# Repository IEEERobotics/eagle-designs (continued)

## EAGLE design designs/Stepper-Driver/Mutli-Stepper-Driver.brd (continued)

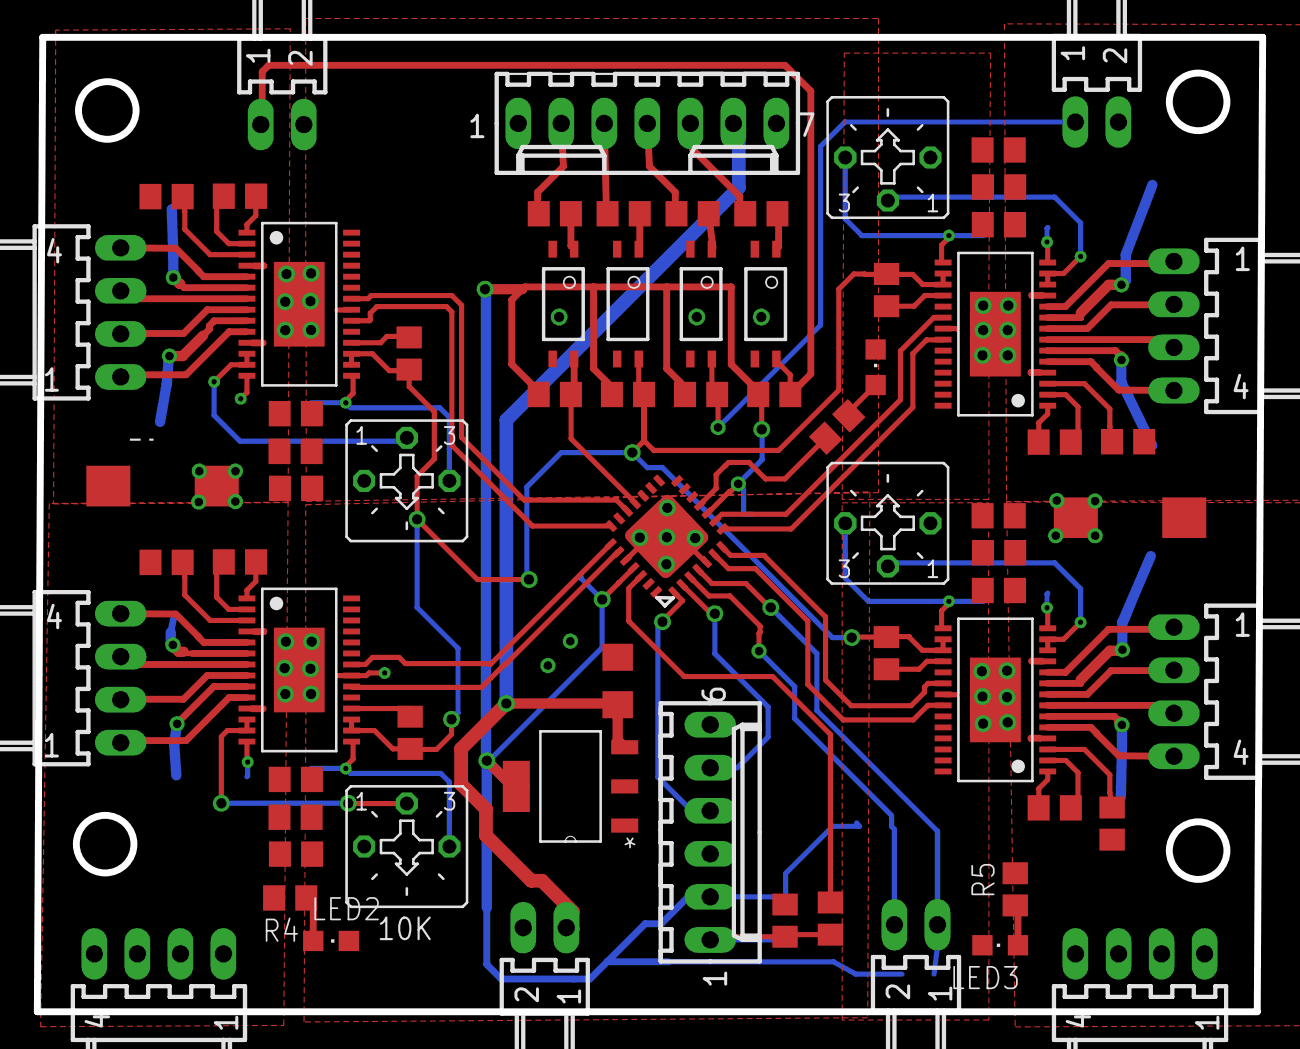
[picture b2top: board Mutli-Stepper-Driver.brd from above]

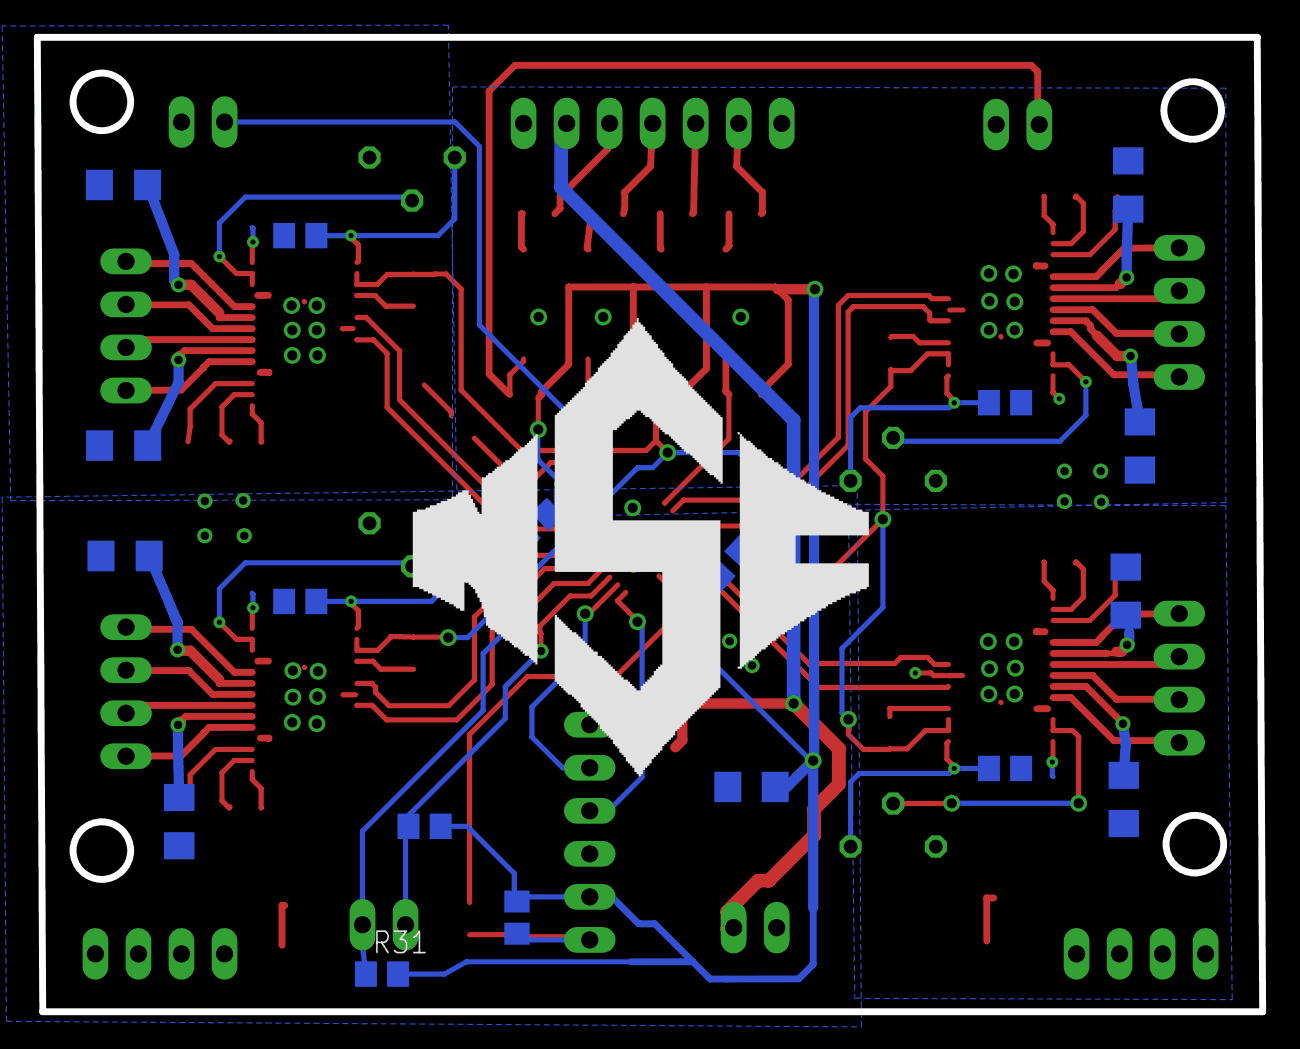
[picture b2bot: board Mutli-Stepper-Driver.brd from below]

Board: 2 copper layers, 72.3 x 57.5 mm, 87 parts (18 on the bottom side), 83 nets.

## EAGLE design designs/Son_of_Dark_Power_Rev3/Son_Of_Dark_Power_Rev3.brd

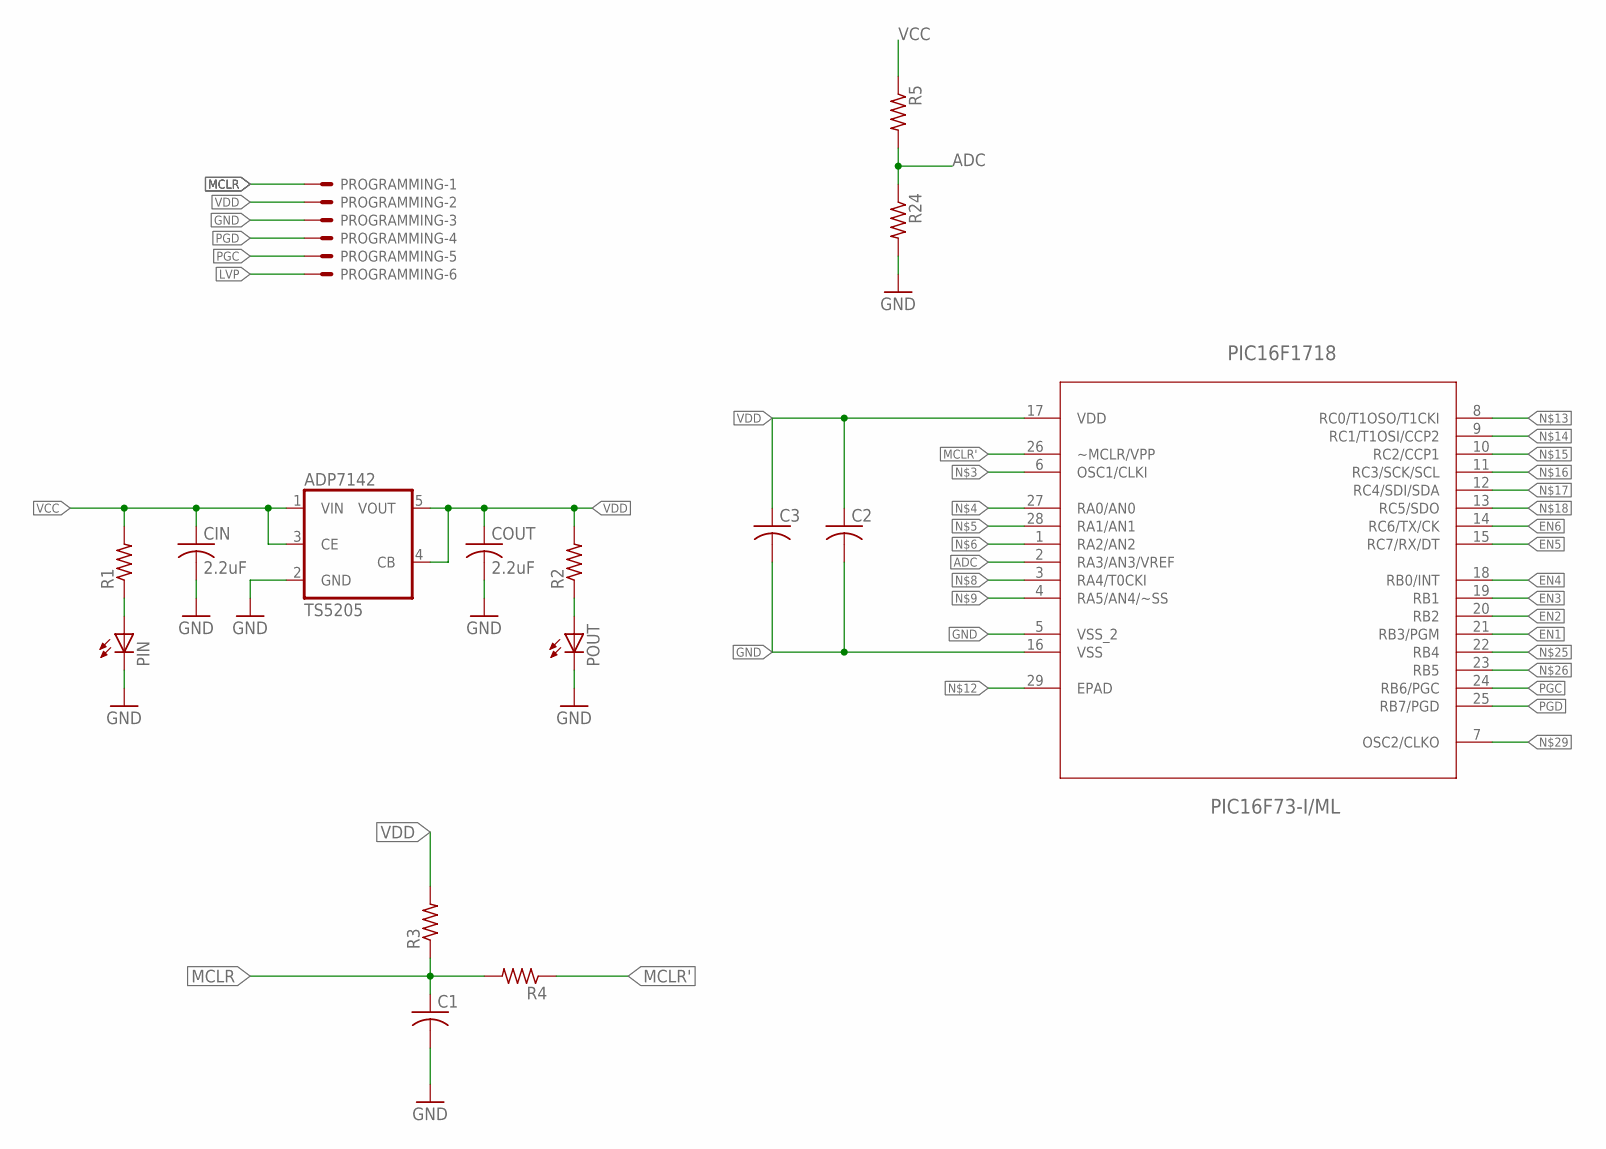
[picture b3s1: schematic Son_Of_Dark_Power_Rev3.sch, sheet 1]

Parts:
ADP7142: TS5205; SOT25
C1, C2, C3: C-USC0805; C0805
CIN: 2.2uF; C1206K
COUT: 2.2uF; C1206K
PIC16F1718: PIC16F73-I/ML; QFN65P600X600X100-28N
PIN: LEDCHIPLED_1206; CHIPLED_1206
POUT: LEDCHIPLED_1206; CHIPLED_1206
PROGRAMMING: 22-23-2061
R1, R2, R3, R4, R5, R24: R-US_R0805; R0805

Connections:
ADC: PIC16F1718.2 (RA3/AN3/VREF), R5.2, R24.1
EN1: PIC16F1718.21 (RB3/PGM); also elsewhere on the board
EN2: PIC16F1718.20 (RB2); also elsewhere on the board
EN3: PIC16F1718.19 (RB1); also elsewhere on the board
EN4: PIC16F1718.18 (RB0/INT); also elsewhere on the board
EN5: PIC16F1718.15 (RC7/RX/DT); also elsewhere on the board
EN6: PIC16F1718.14 (RC6/TX/CK); also elsewhere on the board
GND: ADP7142.2 (GND), C1.2, C2.2, C3.2, CIN.2, COUT.2, PIC16F1718.5 (VSS_2), PIC16F1718.16 (VSS), PIN.C, POUT.C, PROGRAMMING.3, R24.2; also elsewhere on the board
LVP: PROGRAMMING.6
MCLR: C1.1, PROGRAMMING.1, R3.1, R4.2
MCLR': PIC16F1718.26 (~MCLR/VPP), R4.1
unnamed: PIN.A, R1.1
unnamed: POUT.A, R2.1
PGC: PIC16F1718.24 (RB6/PGC), PROGRAMMING.5
PGD: PIC16F1718.25 (RB7/PGD), PROGRAMMING.4
VCC: ADP7142.1 (VIN), ADP7142.3 (CE), CIN.1, R1.2, R5.1; also elsewhere on the board
VDD: ADP7142.4 (CB), ADP7142.5 (VOUT), C2.1, C3.1, COUT.1, PIC16F1718.17 (VDD), PROGRAMMING.2, R2.2, R3.2

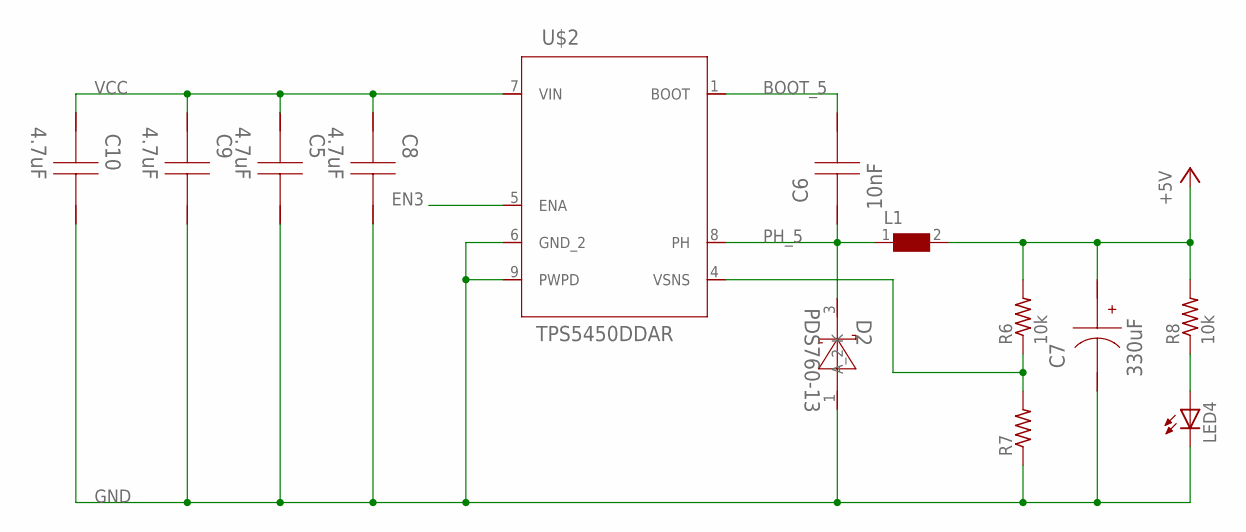
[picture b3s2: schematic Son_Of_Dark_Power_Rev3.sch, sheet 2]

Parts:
C5, C8, C9, C10: 4.7uF; 1206
C6: 10nF; 0805
C7: 330uF; SM_RADIAL_10AMM
D2: PDS760-13; POWERDI5
L1: WE-HCC-7443331000_1090; WE-HCC_1090
LED4: LEDSML1206; SML1206
R6: 10k; R1206
R7: R-US_R1206; R1206
R8: 10k; R0805
U$2: TPS5450DDAR; R-PDSO-G8

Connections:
BOOT_5: C6.1, U$2.1 (BOOT)
EN3: U$2.5 (ENA); also elsewhere on the board
GND: C5.1, C7.2 (-), C8.1, C9.1, C10.1, D2.1 (A_2), LED4.C, R7.1, U$2.6 (GND_2), U$2.9 (PWPD); also elsewhere on the board
unnamed: LED4.A, R8.1
PH_5: C6.2, D2.3 (K), L1.1, U$2.8 (PH)
VCC: C5.2, C8.2, C9.2, C10.2, U$2.7 (VIN); also elsewhere on the board
VOUT_3: C7.1 (+), L1.2, R6.2, R8.2; also elsewhere on the board
VSNS_5: R6.1, R7.2, U$2.4 (VSNS)

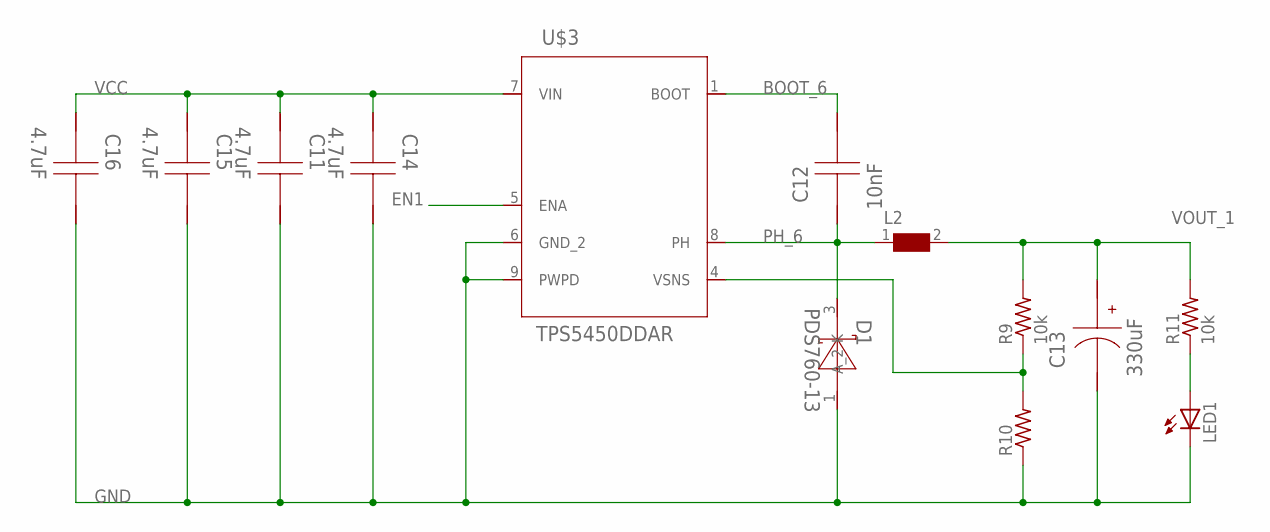
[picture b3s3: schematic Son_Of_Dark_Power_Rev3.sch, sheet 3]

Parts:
C11, C14, C15, C16: 4.7uF; 1206
C12: 10nF; 0805
C13: 330uF; SM_RADIAL_10AMM
D1: PDS760-13; POWERDI5
L2: WE-HCC-7443331000_1090; WE-HCC_1090
LED1: LEDSML1206; SML1206
R9: 10k; R1206
R10: R-US_R1206; R1206
R11: 10k; R0805
U$3: TPS5450DDAR; R-PDSO-G8

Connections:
BOOT_6: C12.1, U$3.1 (BOOT)
EN1: U$3.5 (ENA); also elsewhere on the board
GND: C11.1, C13.2 (-), C14.1, C15.1, C16.1, D1.1 (A_2), LED1.C, R10.1, U$3.6 (GND_2), U$3.9 (PWPD); also elsewhere on the board
unnamed: LED1.A, R11.1
PH_6: C12.2, D1.3 (K), L2.1, U$3.8 (PH)
VCC: C11.2, C14.2, C15.2, C16.2, U$3.7 (VIN); also elsewhere on the board
VOUT_1: C13.1 (+), L2.2, R9.2, R11.2; also elsewhere on the board
VSNS_6: R9.1, R10.2, U$3.4 (VSNS)

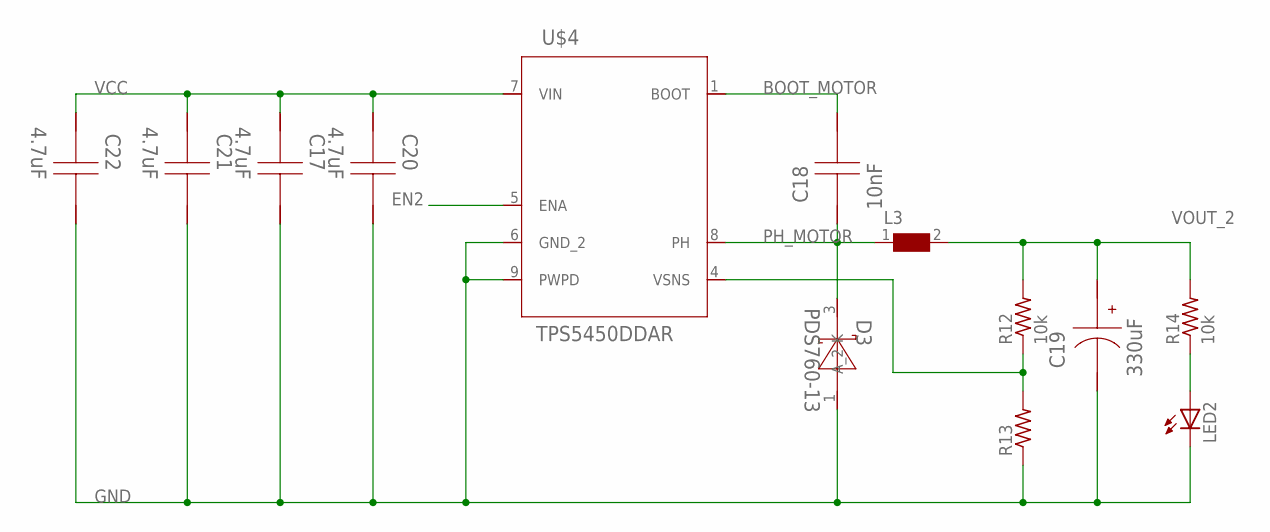
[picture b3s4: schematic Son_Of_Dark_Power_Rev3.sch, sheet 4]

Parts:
C17, C20, C21, C22: 4.7uF; 1206
C18: 10nF; 0805
C19: 330uF; SM_RADIAL_10AMM
D3: PDS760-13; POWERDI5
L3: WE-HCC-7443331000_1090; WE-HCC_1090
LED2: LEDSML1206; SML1206
R12: 10k; R1206
R13: R-US_R1206; R1206
R14: 10k; R0805
U$4: TPS5450DDAR; R-PDSO-G8

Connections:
BOOT_MOTOR: C18.1, U$4.1 (BOOT)
EN2: U$4.5 (ENA); also elsewhere on the board
GND: C17.1, C19.2 (-), C20.1, C21.1, C22.1, D3.1 (A_2), LED2.C, R13.1, U$4.6 (GND_2), U$4.9 (PWPD); also elsewhere on the board
unnamed: LED2.A, R14.1
PH_MOTOR: C18.2, D3.3 (K), L3.1, U$4.8 (PH)
VCC: C17.2, C20.2, C21.2, C22.2, U$4.7 (VIN); also elsewhere on the board
VOUT_2: C19.1 (+), L3.2, R12.2, R14.2; also elsewhere on the board
VSNS1_MOTOR: R12.1, R13.2, U$4.4 (VSNS)

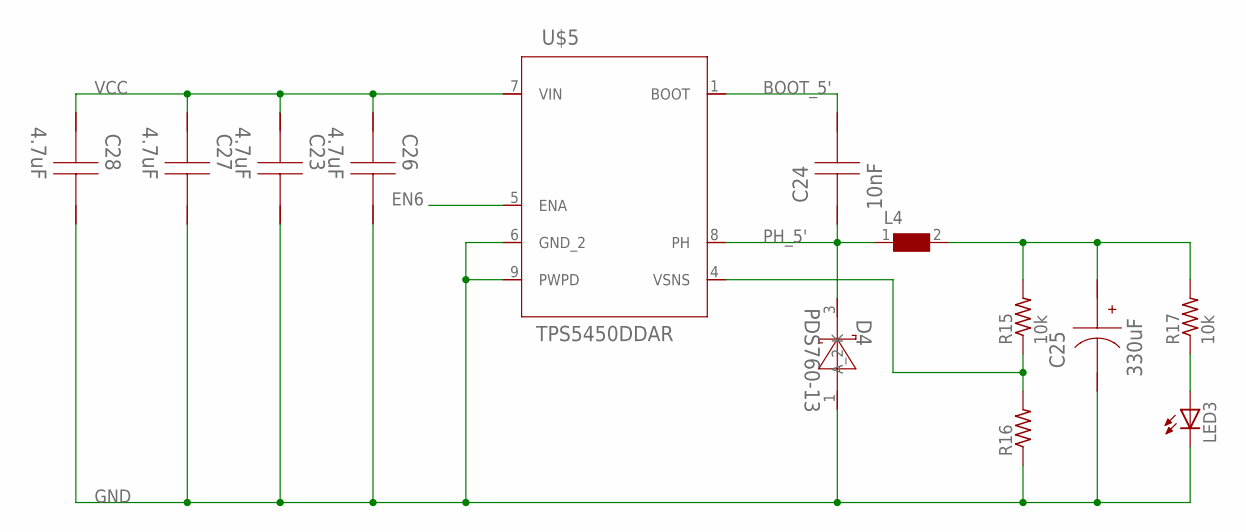
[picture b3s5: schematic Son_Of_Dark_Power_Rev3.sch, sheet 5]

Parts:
C23, C26, C27, C28: 4.7uF; 1206
C24: 10nF; 0805
C25: 330uF; SM_RADIAL_10AMM
D4: PDS760-13; POWERDI5
L4: WE-HCC-7443331000_1090; WE-HCC_1090
LED3: LEDSML1206; SML1206
R15: 10k; R1206
R16: R-US_R1206; R1206
R17: 10k; R0805
U$5: TPS5450DDAR; R-PDSO-G8

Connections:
BOOT_5': C24.1, U$5.1 (BOOT)
EN6: U$5.5 (ENA); also elsewhere on the board
GND: C23.1, C25.2 (-), C26.1, C27.1, C28.1, D4.1 (A_2), LED3.C, R16.1, U$5.6 (GND_2), U$5.9 (PWPD); also elsewhere on the board
unnamed: LED3.A, R17.1
PH_5': C24.2, D4.3 (K), L4.1, U$5.8 (PH)
VCC: C23.2, C26.2, C27.2, C28.2, U$5.7 (VIN); also elsewhere on the board
VOUT_6: C25.1 (+), L4.2, R15.2, R17.2; also elsewhere on the board
VSNS_1': R15.1, R16.2, U$5.4 (VSNS)

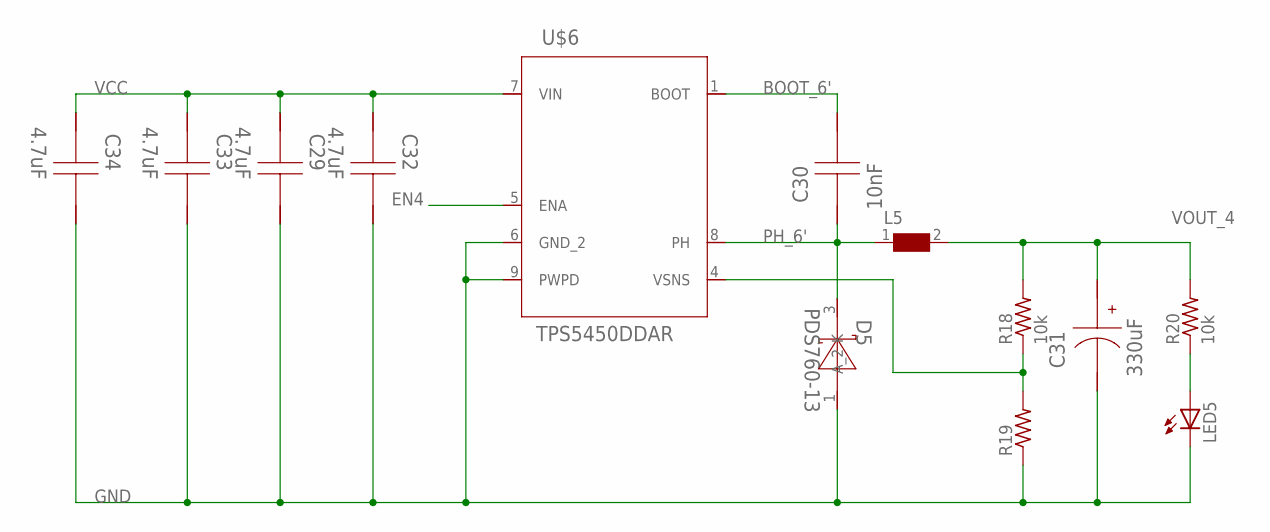
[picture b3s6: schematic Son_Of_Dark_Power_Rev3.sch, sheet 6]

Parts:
C29, C32, C33, C34: 4.7uF; 1206
C30: 10nF; 0805
C31: 330uF; SM_RADIAL_10AMM
D5: PDS760-13; POWERDI5
L5: WE-HCC-7443331000_1090; WE-HCC_1090
LED5: LEDSML1206; SML1206
R18: 10k; R1206
R19: R-US_R1206; R1206
R20: 10k; R0805
U$6: TPS5450DDAR; R-PDSO-G8

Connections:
BOOT_6': C30.1, U$6.1 (BOOT)
EN4: U$6.5 (ENA); also elsewhere on the board
GND: C29.1, C31.2 (-), C32.1, C33.1, C34.1, D5.1 (A_2), LED5.C, R19.1, U$6.6 (GND_2), U$6.9 (PWPD); also elsewhere on the board
unnamed: LED5.A, R20.1
PH_6': C30.2, D5.3 (K), L5.1, U$6.8 (PH)
VCC: C29.2, C32.2, C33.2, C34.2, U$6.7 (VIN); also elsewhere on the board
VOUT_4: C31.1 (+), L5.2, R18.2, R20.2; also elsewhere on the board
VSNS_2': R18.1, R19.2, U$6.4 (VSNS)

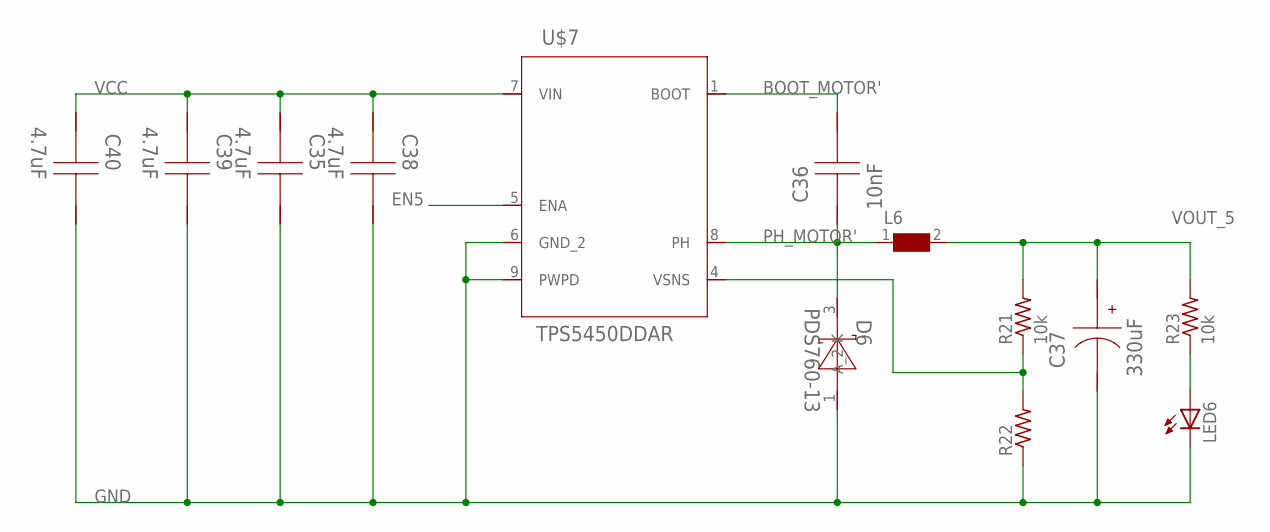
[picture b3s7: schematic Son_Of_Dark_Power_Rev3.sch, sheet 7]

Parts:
C35, C38, C39, C40: 4.7uF; 1206
C36: 10nF; 0805
C37: 330uF; SM_RADIAL_10AMM
D6: PDS760-13; POWERDI5
L6: WE-HCC-7443331000_1090; WE-HCC_1090
LED6: LEDSML1206; SML1206
R21: 10k; R1206
R22: R-US_R1206; R1206
R23: 10k; R0805
U$7: TPS5450DDAR; R-PDSO-G8

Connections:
BOOT_MOTOR': C36.1, U$7.1 (BOOT)
EN5: U$7.5 (ENA); also elsewhere on the board
GND: C35.1, C37.2 (-), C38.1, C39.1, C40.1, D6.1 (A_2), LED6.C, R22.1, U$7.6 (GND_2), U$7.9 (PWPD); also elsewhere on the board
unnamed: LED6.A, R23.1
PH_MOTOR': C36.2, D6.3 (K), L6.1, U$7.8 (PH)
VCC: C35.2, C38.2, C39.2, C40.2, U$7.7 (VIN); also elsewhere on the board
VOUT_5: C37.1 (+), L6.2, R21.2, R23.2; also elsewhere on the board
VSNS1_MOTOR1': R21.1, R22.2, U$7.4 (VSNS)

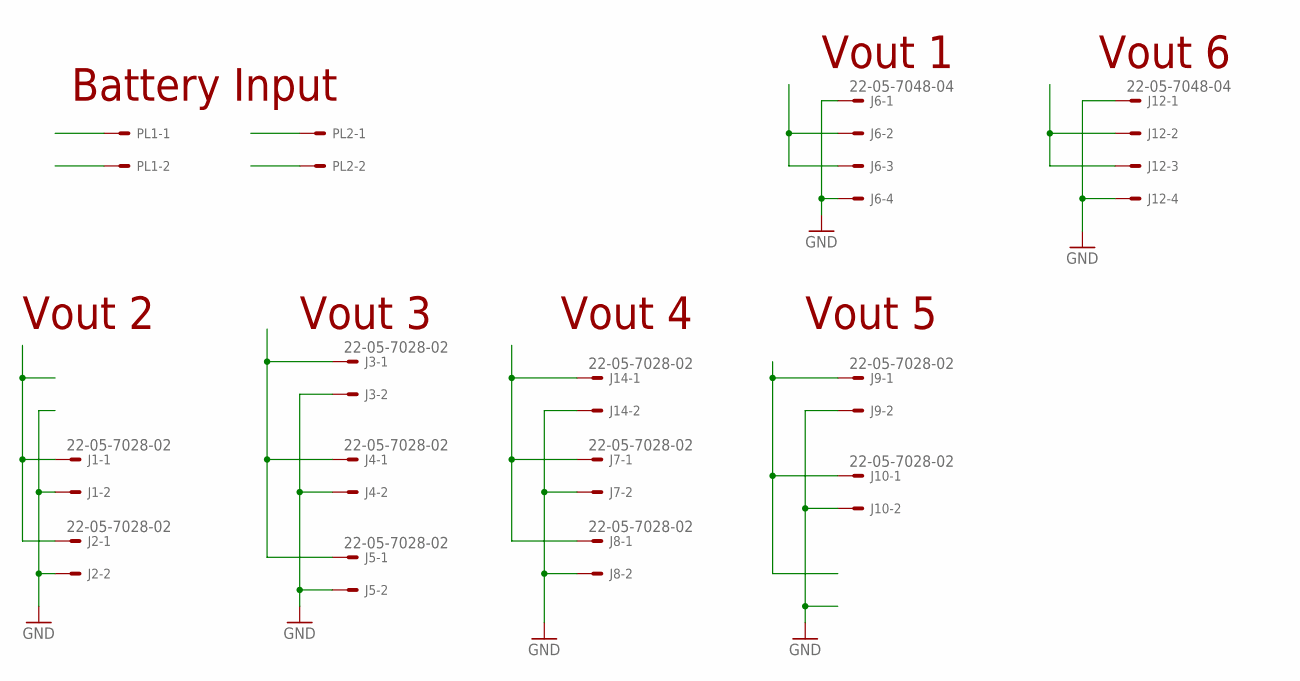
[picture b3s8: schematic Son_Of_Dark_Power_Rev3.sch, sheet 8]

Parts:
J1, J2, J3, J4, J5, J7, J8, J9, J10, J14: 22-05-7028-02; 7395-02
J6, J12: 22-05-7048-04; 7395-04
PL1, PL2: 555X-2H; 5569-2

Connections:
GND: J1.2, J2.2, J3.2, J4.2, J5.2, J6.1, J6.4, J7.2, J8.2, J9.2, J10.2, J12.1, J12.4, J14.2, PL1.1, PL2.1; also elsewhere on the board
VCC: PL1.2, PL2.2; also elsewhere on the board
VOUT_1: J6.2, J6.3; also elsewhere on the board
VOUT_2: J1.1, J2.1; also elsewhere on the board
VOUT_3: J3.1, J4.1, J5.1; also elsewhere on the board
VOUT_4: J7.1, J8.1, J14.1; also elsewhere on the board
VOUT_5: J9.1, J10.1; also elsewhere on the board
VOUT_6: J12.2, J12.3; also elsewhere on the board

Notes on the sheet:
Battery Input
Vout 1
Vout 2
Vout 3
Vout 4
Vout 5
Vout 6

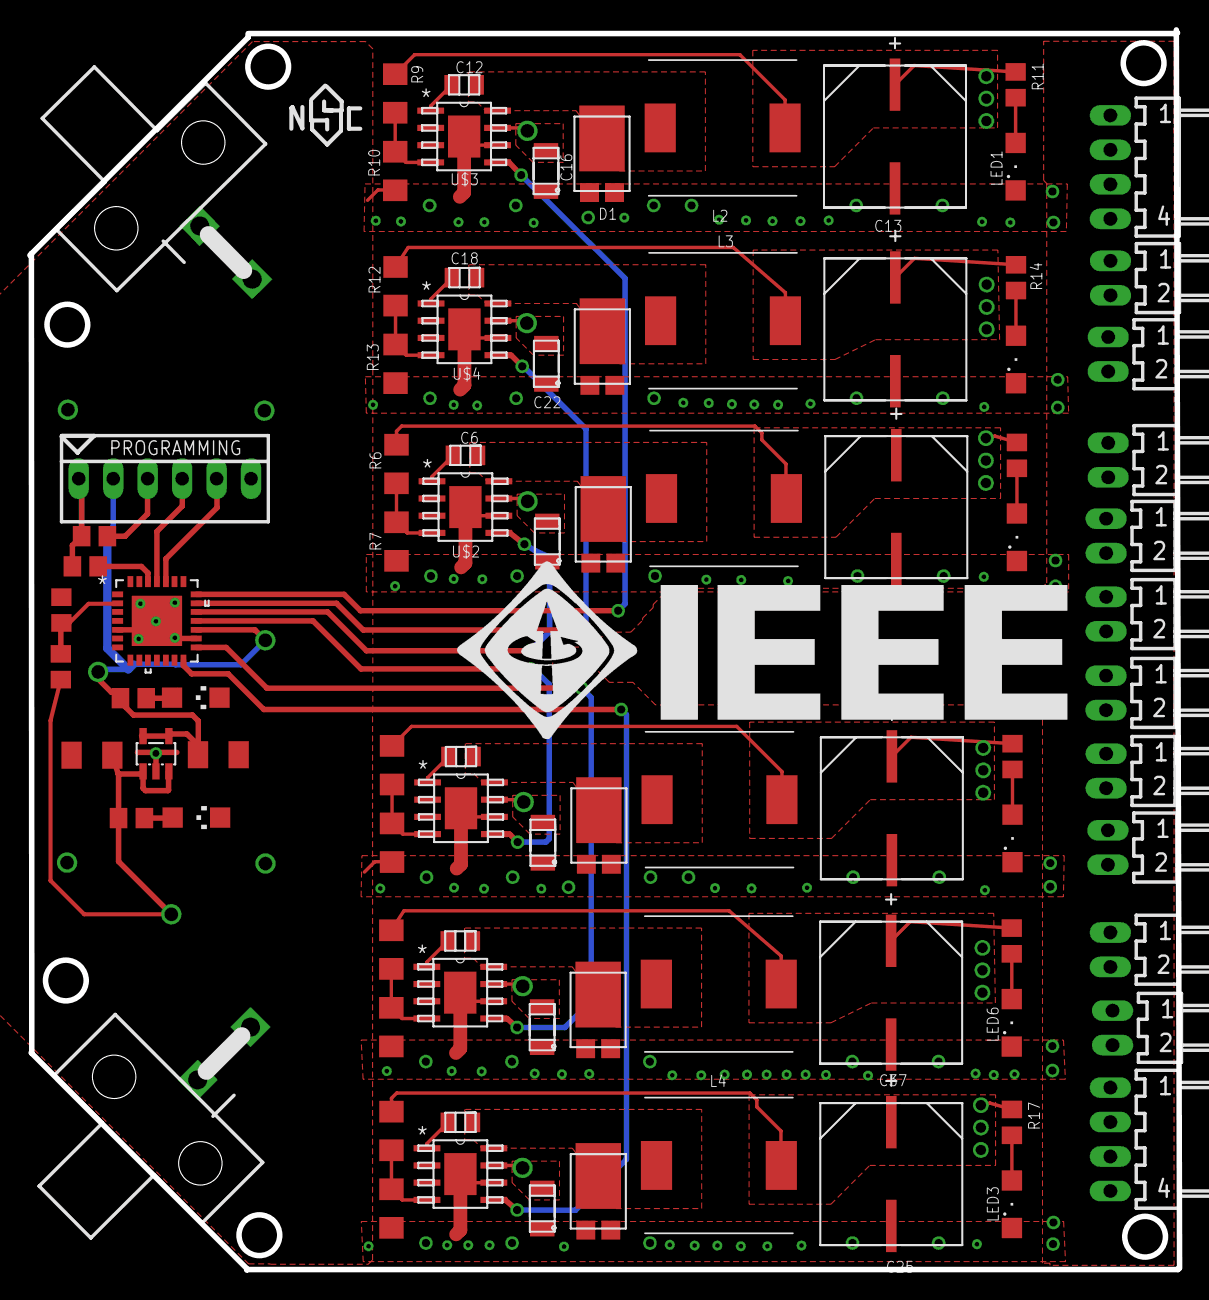
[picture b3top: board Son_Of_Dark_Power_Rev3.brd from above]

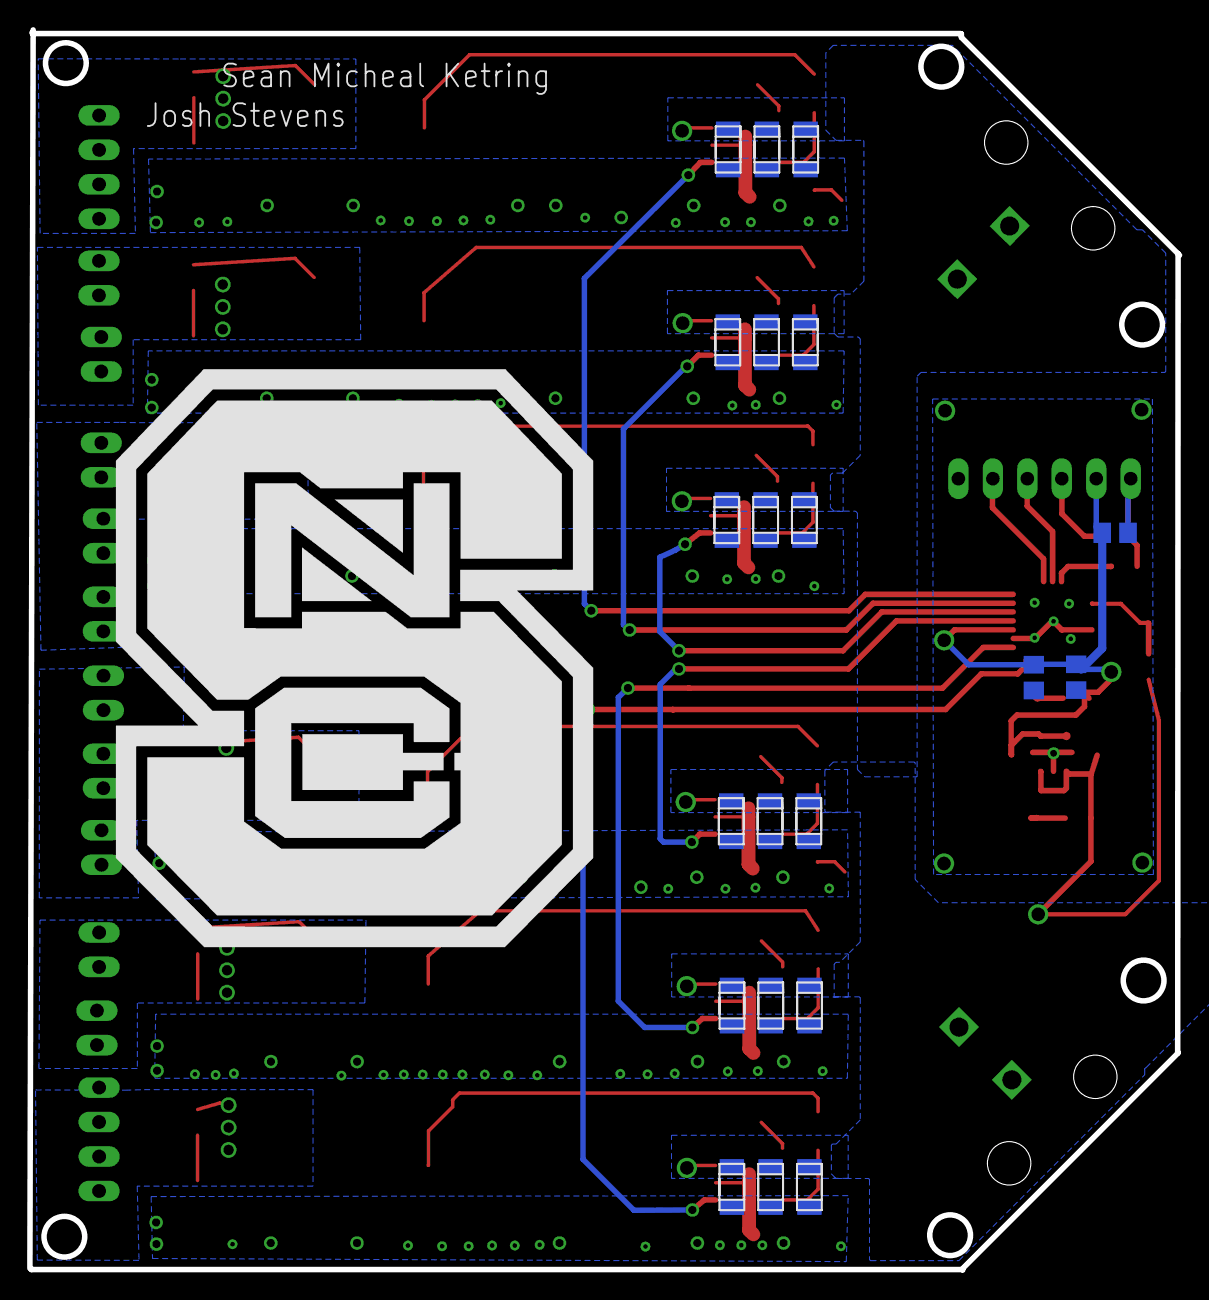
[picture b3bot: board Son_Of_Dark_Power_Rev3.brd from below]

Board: 2 copper layers, 84.7 x 91.4 mm, 108 parts (21 on the bottom side), 46 nets.

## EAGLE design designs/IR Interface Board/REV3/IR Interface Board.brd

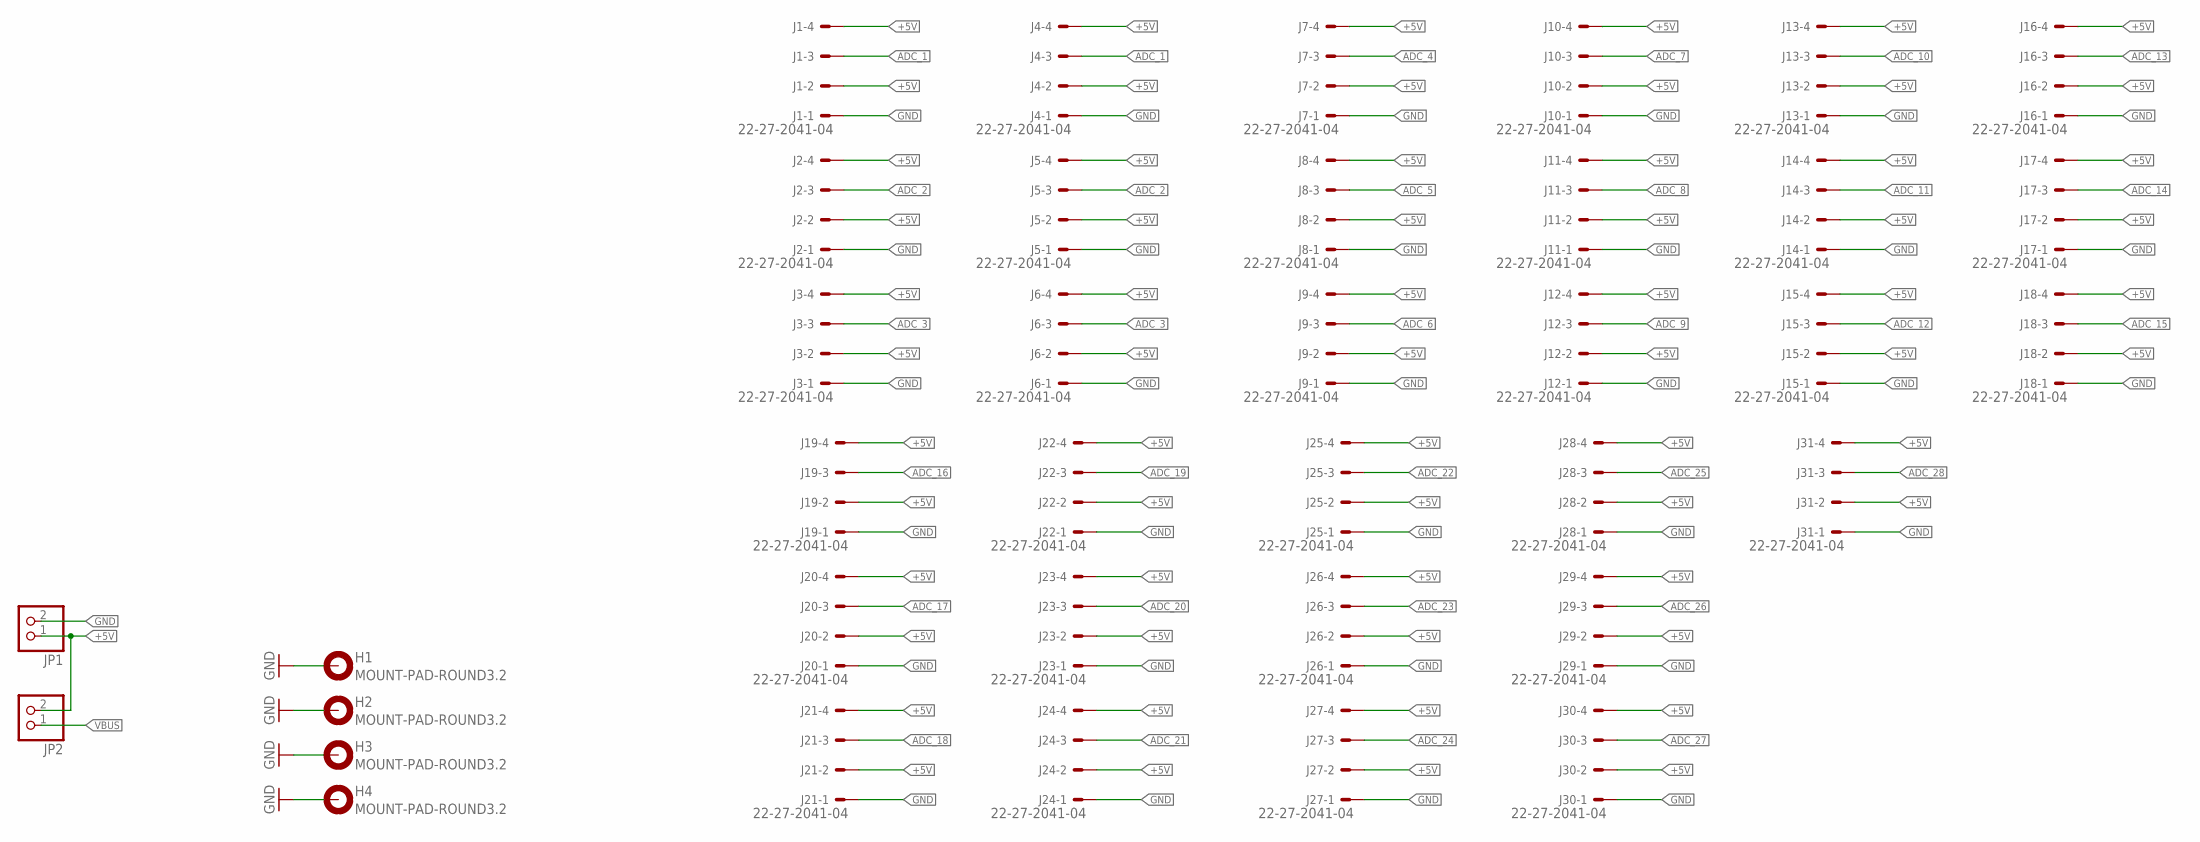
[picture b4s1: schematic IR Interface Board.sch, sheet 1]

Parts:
H1, H2, H3, H4: MOUNT-PAD-ROUND3.2; 3,2-PAD
J1, J2, J3, J4, J5, J6, J7, J8, J9, J10, J11, J12, J13, J14, J15, J16, J17, J18, J19, J20, J21, J22, J23, J24, J25, J26, J27, J28, J29, J30, J31: 22-27-2041-04; 6410-04
JP1, JP2: PINHD-1X2; 1X02

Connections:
+5V: J1.2, J1.4, J2.2, J2.4, J3.2, J3.4, J4.2, J4.4, J5.2, J5.4, J6.2, J6.4, J7.2, J7.4, J8.2, J8.4, J9.2, J9.4, J10.2, J10.4, J11.2, J11.4, J12.2, J12.4, J13.2, J13.4, J14.2, J14.4, J15.2, J15.4, J16.2, J16.4, J17.2, J17.4, J18.2, J18.4, J19.2, J19.4, J20.2, J20.4, J21.2, J21.4, J22.2, J22.4, J23.2, J23.4, J24.2, J24.4, J25.2, J25.4, J26.2, J26.4, J27.2, J27.4, J28.2, J28.4, J29.2, J29.4, J30.2, J30.4, J31.2, J31.4, JP1.1, JP2.2; also elsewhere on the board
ADC_1: J1.3, J4.3; also elsewhere on the board
ADC_2: J2.3, J5.3; also elsewhere on the board
ADC_3: J3.3, J6.3; also elsewhere on the board
ADC_4: J7.3; also elsewhere on the board
ADC_5: J8.3; also elsewhere on the board
ADC_6: J9.3; also elsewhere on the board
ADC_7: J10.3; also elsewhere on the board
ADC_8: J11.3; also elsewhere on the board
ADC_9: J12.3; also elsewhere on the board
ADC_10: J13.3; also elsewhere on the board
ADC_11: J14.3; also elsewhere on the board
ADC_12: J15.3; also elsewhere on the board
ADC_13: J16.3; also elsewhere on the board
ADC_14: J17.3; also elsewhere on the board
ADC_15: J18.3; also elsewhere on the board
ADC_16: J19.3; also elsewhere on the board
ADC_17: J20.3; also elsewhere on the board
ADC_18: J21.3; also elsewhere on the board
ADC_19: J22.3; also elsewhere on the board
ADC_20: J23.3; also elsewhere on the board
ADC_21: J24.3; also elsewhere on the board
ADC_22: J25.3; also elsewhere on the board
ADC_23: J26.3; also elsewhere on the board
ADC_24: J27.3; also elsewhere on the board
ADC_25: J28.3; also elsewhere on the board
ADC_26: J29.3; also elsewhere on the board
ADC_27: J30.3; also elsewhere on the board
ADC_28: J31.3; also elsewhere on the board
GND: H1.B3,2, H2.B3,2, H3.B3,2, H4.B3,2, J1.1, J2.1, J3.1, J4.1, J5.1, J6.1, J7.1, J8.1, J9.1, J10.1, J11.1, J12.1, J13.1, J14.1, J15.1, J16.1, J17.1, J18.1, J19.1, J20.1, J21.1, J22.1, J23.1, J24.1, J25.1, J26.1, J27.1, J28.1, J29.1, J30.1, J31.1, JP1.2; also elsewhere on the board
VBUS: JP2.1; also elsewhere on the board
